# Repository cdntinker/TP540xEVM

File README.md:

# TPS540x Evaluation Board

(This project started as a result of the truly awful EVM design from TI for these chips.)

This little circuit should work with either the TPS5403 or TPS5405 from Texas Instruments.

Both chips will accept up to 28V input.

The TPS5403 wants 4.5-28V & outputs 3v3 up to 1.7A.

The TPS5405 wants 6.5-28V & outputs 5v0 up to 2A.

# The 3 boards

## Standalone
Basically, a standalone voltage regulator board...

## Module
A tiny little voltage regulator module (daughterboard)...

There is also a symbol/footprint/3D model set in ***KiCAD Customs*** for this module.

## Carrier
Like **Standalone**, but using **Module** instead of parts on the board...

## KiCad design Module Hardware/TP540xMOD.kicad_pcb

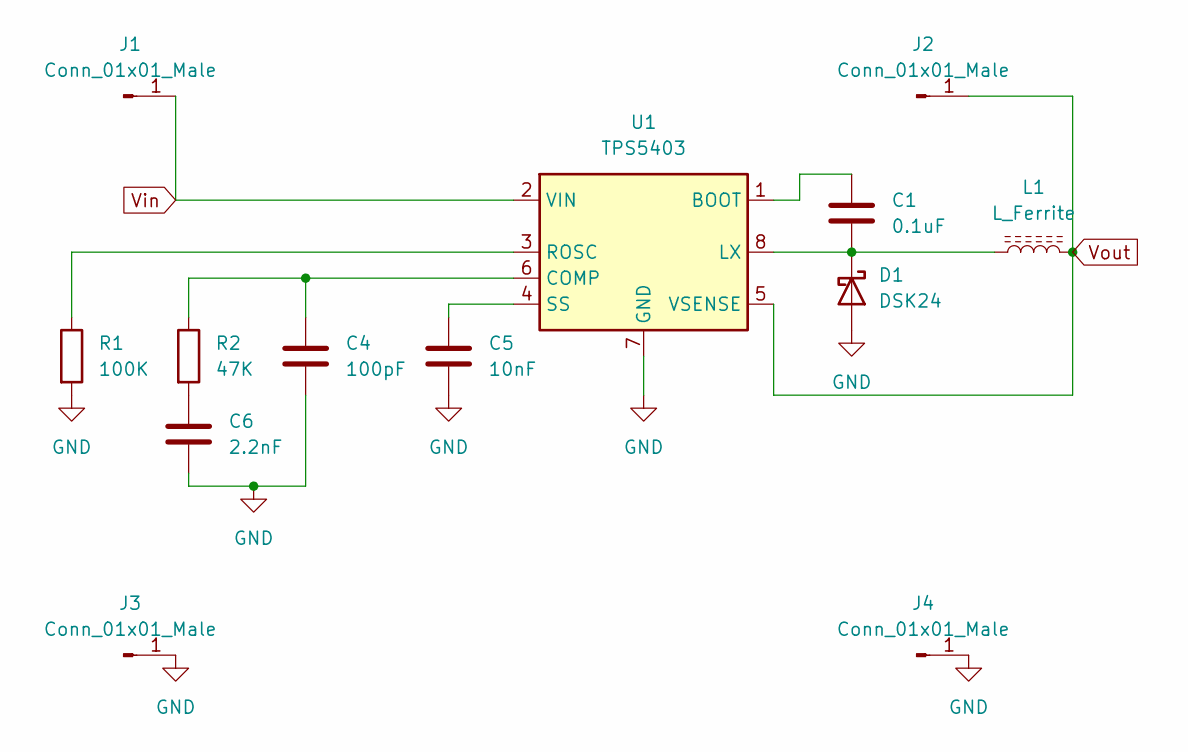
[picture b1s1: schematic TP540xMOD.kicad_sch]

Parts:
C1: 0.1uF; C_0603_1608Metric
C4: 100pF; C_0603_1608Metric
C5: 10nF; C_0603_1608Metric
C6: 2.2nF; C_0603_1608Metric
D1: DSK24; D_SOD-123; LCSC C908229
J1, J2, J3, J4: Conn_01x01_Male; ConnPoint
L1: L_Ferrite; IND-SMD_L7.1-W6.6; LCSC C2983095
R1: 100K; R_0603_1608Metric
R2: 47K; R_0603_1608Metric
U1: TPS5403; SOIC-8_3.9x4.9mm_P1.27mm

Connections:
GND: C4.2, C5.2, C6.2, D1.2 (A), J3.1, J4.1, R1.2, U1.7 (GND)
unnamed: C1.1, U1.1 (BOOT)
unnamed: C1.2, D1.1 (K), L1.1, U1.8 (LX)
unnamed: C4.1, R2.1, U1.6 (COMP)
unnamed: C5.1, U1.4 (SS)
unnamed: C6.1, R2.2
unnamed: R1.1, U1.3 (ROSC)
Vin: J1.1, U1.2 (VIN)
Vout: J2.1, L1.2, U1.5 (VSENSE)

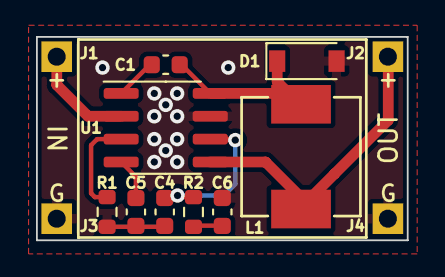
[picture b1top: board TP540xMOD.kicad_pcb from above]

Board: 2 copper layers, 20.6 x 11.3 mm, 13 parts (0 on the bottom side), 9 nets.

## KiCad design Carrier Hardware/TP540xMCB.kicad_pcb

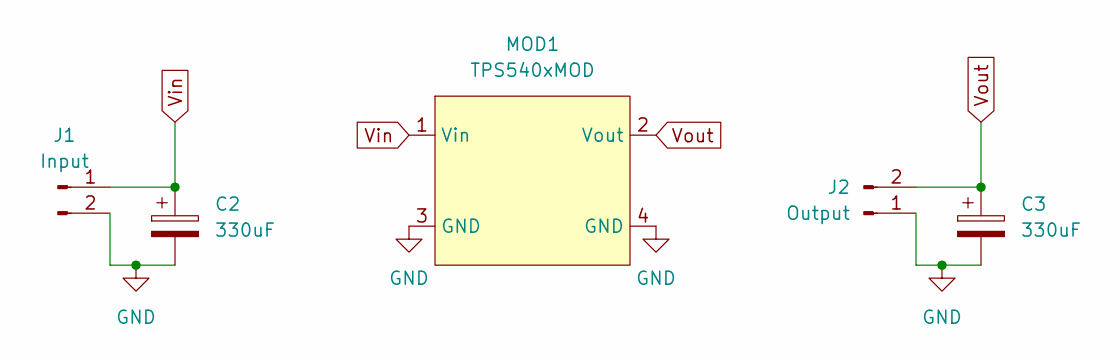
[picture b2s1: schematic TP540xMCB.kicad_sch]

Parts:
C2, C3: 330uF; CP_Elec_8x10; LCSC C178599
J1: Input; TerminalBlock_4Ucon_1x02_P3.50mm_Horizontal; LCSC C784940
J2: Output; TerminalBlock_4Ucon_1x02_P3.50mm_Horizontal; LCSC C784940
MOD1: TPS540xMOD

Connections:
GND: C2.2, C3.2, J1.2, J2.1, MOD1.3 (GND), MOD1.4 (GND)
Vin: C2.1, J1.1, MOD1.1 (Vin)
Vout: C3.1, J2.2, MOD1.2 (Vout)

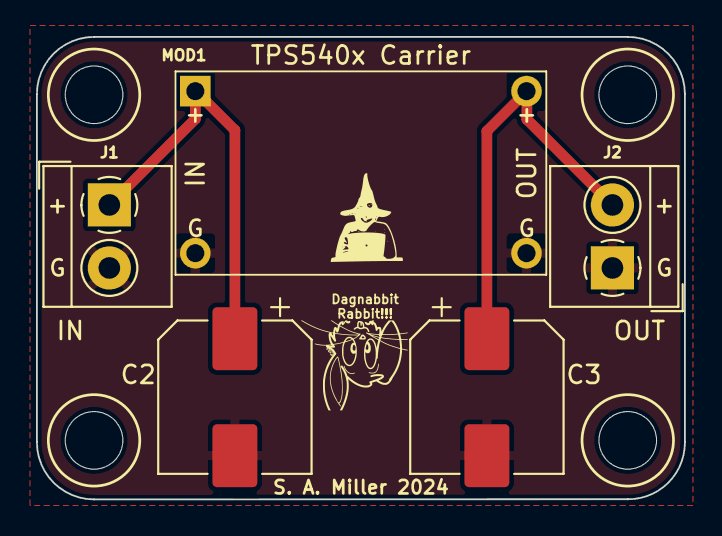
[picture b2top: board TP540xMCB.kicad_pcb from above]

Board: 2 copper layers, 36.0 x 25.7 mm, 5 parts (0 on the bottom side), 3 nets.

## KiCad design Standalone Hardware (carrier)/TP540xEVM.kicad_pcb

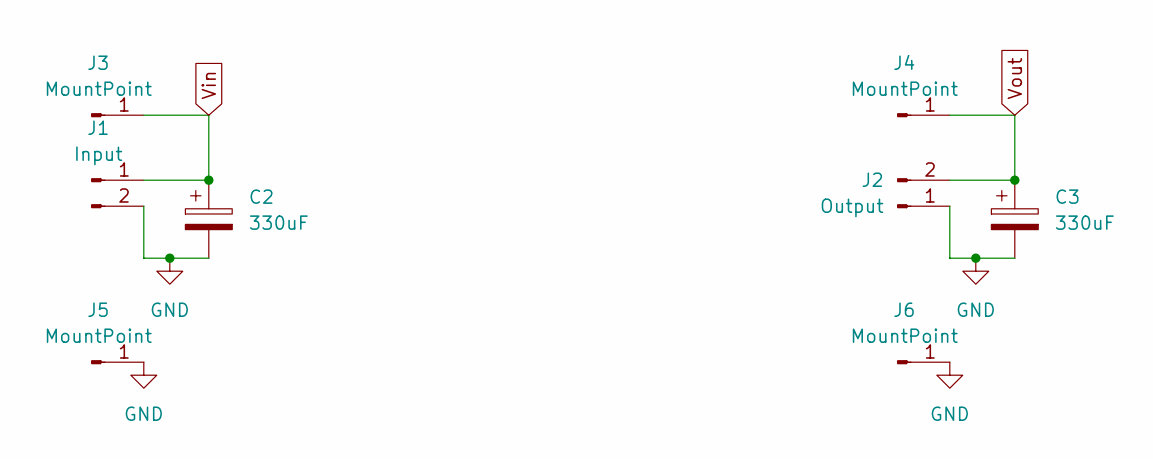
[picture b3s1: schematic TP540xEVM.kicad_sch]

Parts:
C2, C3: 330uF; CP_Elec_8x10; LCSC C178599
J1: Input; TerminalBlock_4Ucon_1x02_P3.50mm_Horizontal; LCSC C784940
J2: Output; TerminalBlock_4Ucon_1x02_P3.50mm_Horizontal; LCSC C784940
J3, J4, J5, J6: MountPoint; ConnPoint

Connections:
GND: C2.2, C3.2, J1.2, J2.1, J5.1, J6.1
Vin: C2.1, J1.1, J3.1
Vout: C3.1, J2.2, J4.1

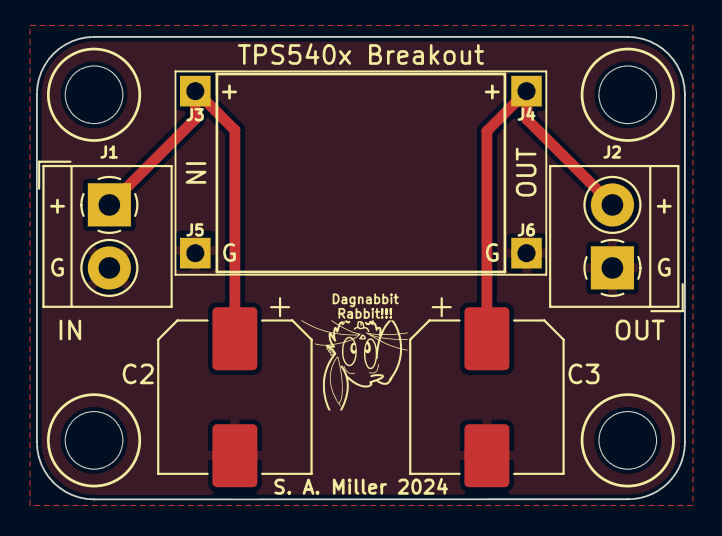
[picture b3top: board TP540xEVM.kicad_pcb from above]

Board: 2 copper layers, 36.0 x 25.7 mm, 8 parts (0 on the bottom side), 3 nets.

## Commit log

2024-03-06 Now with a "module" version...
2024-03-07 w00t...SMD inductor
2024-03-07 Created symbol, footprint, 3D for Module
2024-03-08 Some cleanup...
2024-03-08 bye bye bloody wrl file(s) (at least the custom ones)
2024-03-09 bye bye bloody wrl files
